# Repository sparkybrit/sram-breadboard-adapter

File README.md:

# sram-breadboard-adapter

An 8 MB SRAM board for a breadboard: eight Lyontek LY62W10248ML (1M × 8, TSOP-II-44) in two banks of
four, on a 4-layer board with +5V and GND planes. J0 carries the address and control lines, J1 the data.
Built for [Sparky1](https://github.com/sparkybrit/sparky1), a 68030 breadboard computer.

## Things the KiCad files do not tell you

**The byte lanes are numbered for a little-endian CPU.** In each bank, chip 0 is on D7–D0 and chip 3 on
D31–D24:

| Chip enable | J0 pin | Data lines |
|---|---|---|
| `/CEA0`, `/CEB0` | 24, 28 | D7–D0 |
| `/CEA1`, `/CEB1` | 25, 29 | D15–D8 |
| `/CEA2`, `/CEB2` | 26, 30 | D23–D16 |
| `/CEA3`, `/CEB3` | 27, 31 | D31–D24 |

The 68030 is big-endian: its byte 0 is on D31–D24. So on Sparky1 the chip selects are crossed over on the
breadboard: the select for the CPU's lane 0 goes to `/CEx3`, lane 1 to `/CEx2`, and so on. The data pins are
wired straight, D0 to D0.

**The fitted board has extra bypass capacitors that are not in the layout.** 100 nF 0402 parts were soldered
by hand straight across the supply pins of each RAM chip (2026-10-02; Sparky1's notes record one across
pins 11/12 and one across 33/34 on all eight). The layout's own capacitors sit off the end of each package,
too far from the pins: with them alone the board gave an occasional single-bit read error, and with the
extra ones it ran 127 hours clean. A new revision should place two capacitors per chip under the pins; see
"Improve decoupling capacitor placement" in Sparky1's `CLAUDE.md`.

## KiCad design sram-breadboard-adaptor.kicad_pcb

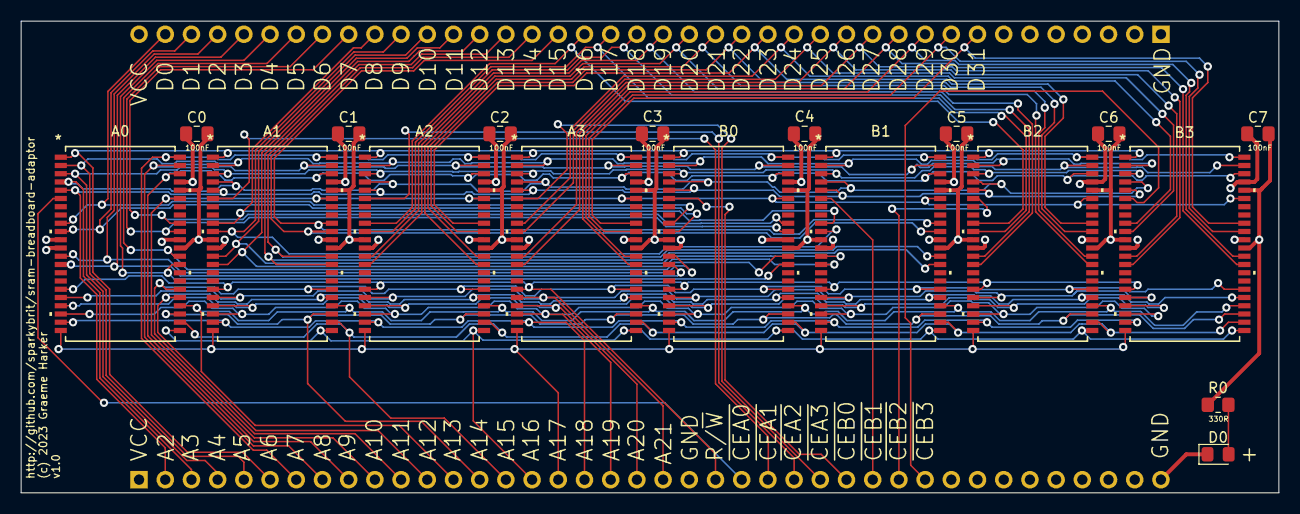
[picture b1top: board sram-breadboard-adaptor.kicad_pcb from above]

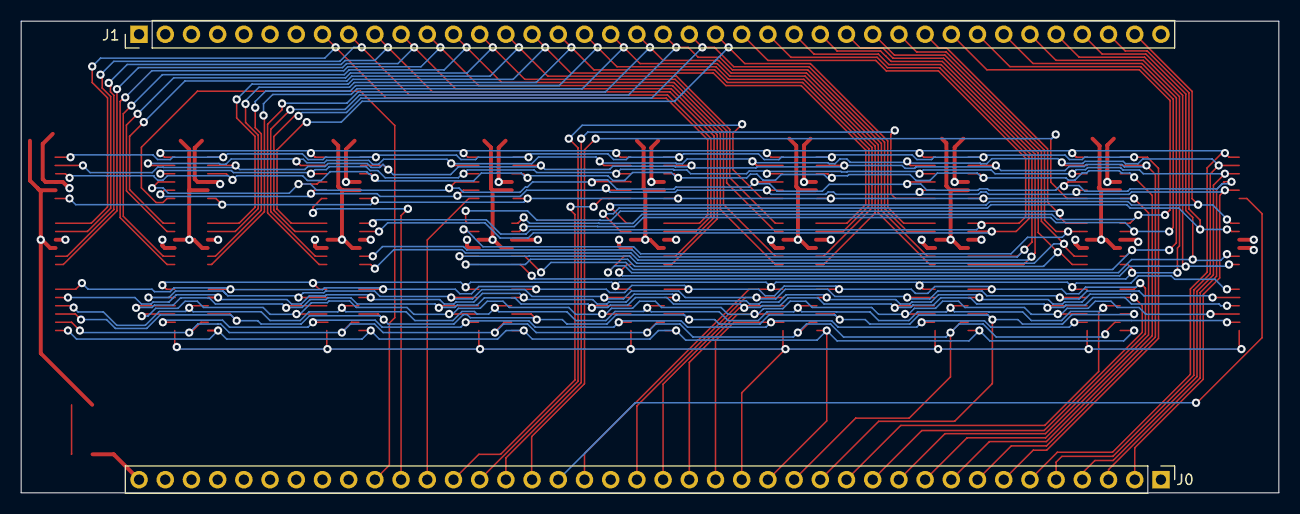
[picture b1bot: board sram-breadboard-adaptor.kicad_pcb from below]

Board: 4 copper layers, 121.9 x 45.7 mm, 20 parts (2 on the bottom side), 64 nets.

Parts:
A0, A1, A2, A3: LY62W10248ML-55LLI; TSOP-II-44_400MIL_LTK
B0, B1, B2, B3: LY62W10248ML-55LLI; TSOP-II-44_400MIL_LTK
C0, C2, C3, C4, C5, C6, C7: 100nF; C_0805_2012Metric_Pad1.18x1.45mm_HandSolder
C1: 110nF; C_0805_2012Metric_Pad1.18x1.45mm_HandSolder
D0: LED; LED_0805_2012Metric_Pad1.15x1.40mm_HandSolder
J0, J1: Conn_01x40; PinHeader_1x40_P2.54mm_Vertical
R0: 330R; R_0805_2012Metric_Pad1.20x1.40mm_HandSolder

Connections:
+5V: A0.11 (VCC), A0.33 (VCC), A0.40 (CE2), A1.11 (VCC), A1.33 (VCC), A1.40 (CE2), A2.11 (VCC), A2.33 (VCC), A2.40 (CE2), A3.11 (VCC), A3.33 (VCC), A3.40 (CE2), B0.11 (VCC), B0.33 (VCC), B0.40 (CE2), B1.11 (VCC), B1.33 (VCC), B1.40 (CE2), B2.11 (VCC), B2.33 (VCC), B2.40 (CE2), B3.11 (VCC), B3.33 (VCC), B3.40 (CE2), C0.1, C1.1, C2.1, C3.1, C4.1, C5.1, C6.1, C7.1, J0.1, J1.40, R0.1
/A2: A0.5 (A0), A1.5 (A0), A2.5 (A0), A3.5 (A0), B0.5 (A0), B1.5 (A0), B2.5 (A0), B3.5 (A0), J0.2
/A3: A0.4 (A1), A1.4 (A1), A2.4 (A1), A3.4 (A1), B0.4 (A1), B1.4 (A1), B2.4 (A1), B3.4 (A1), J0.3
/A4: A0.3 (A2), A1.3 (A2), A2.3 (A2), A3.3 (A2), B0.3 (A2), B1.3 (A2), B2.3 (A2), B3.3 (A2), J0.4
/A5: A0.2 (A3), A1.2 (A3), A2.2 (A3), A3.2 (A3), B0.2 (A3), B1.2 (A3), B2.2 (A3), B3.2 (A3), J0.5
/A6: A0.1 (A4), A1.1 (A4), A2.1 (A4), A3.1 (A4), B0.1 (A4), B1.1 (A4), B2.1 (A4), B3.1 (A4), J0.6
/A7: A0.44 (A5), A1.44 (A5), A2.44 (A5), A3.44 (A5), B0.44 (A5), B1.44 (A5), B2.44 (A5), B3.44 (A5), J0.7
/A8: A0.43 (A6), A1.43 (A6), A2.43 (A6), A3.43 (A6), B0.43 (A6), B1.43 (A6), B2.43 (A6), B3.43 (A6), J0.8
/A9: A0.42 (A7), A1.42 (A7), A2.42 (A7), A3.42 (A7), B0.42 (A7), B1.42 (A7), B2.42 (A7), B3.42 (A7), J0.9
/A10: A0.39 (A8), A1.39 (A8), A2.39 (A8), A3.39 (A8), B0.39 (A8), B1.39 (A8), B2.39 (A8), B3.39 (A8), J0.10
/A11: A0.28 (A9), A1.28 (A9), A2.28 (A9), A3.28 (A9), B0.28 (A9), B1.28 (A9), B2.28 (A9), B3.28 (A9), J0.11
/A12: A0.27 (A10), A1.27 (A10), A2.27 (A10), A3.27 (A10), B0.27 (A10), B1.27 (A10), B2.27 (A10), B3.27 (A10), J0.12
/A13: A0.26 (A11), A1.26 (A11), A2.26 (A11), A3.26 (A11), B0.26 (A11), B1.26 (A11), B2.26 (A11), B3.26 (A11), J0.13
/A14: A0.25 (A12), A1.25 (A12), A2.25 (A12), A3.25 (A12), B0.25 (A12), B1.25 (A12), B2.25 (A12), B3.25 (A12), J0.14
/A15: A0.24 (A13), A1.24 (A13), A2.24 (A13), A3.24 (A13), B0.24 (A13), B1.24 (A13), B2.24 (A13), B3.24 (A13), J0.15
/A16: A0.23 (A14), A1.23 (A14), A2.23 (A14), A3.23 (A14), B0.23 (A14), B1.23 (A14), B2.23 (A14), B3.23 (A14), J0.16
/A17: A0.22 (A15), A1.22 (A15), A2.22 (A15), A3.22 (A15), B0.22 (A15), B1.22 (A15), B2.22 (A15), B3.22 (A15), J0.17
/A18: A0.21 (A16), A1.21 (A16), A2.21 (A16), A3.21 (A16), B0.21 (A16), B1.21 (A16), B2.21 (A16), B3.21 (A16), J0.18
/A19: A0.20 (A17), A1.20 (A17), A2.20 (A17), A3.20 (A17), B0.20 (A17), B1.20 (A17), B2.20 (A17), B3.20 (A17), J0.19
/A20: A0.19 (A18), A1.19 (A18), A2.19 (A18), A3.19 (A18), B0.19 (A18), B1.19 (A18), B2.19 (A18), B3.19 (A18), J0.20
/A21: A0.18 (A19), A1.18 (A19), A2.18 (A19), A3.18 (A19), B0.18 (A19), B1.18 (A19), B2.18 (A19), B3.18 (A19), J0.21
/D0: A0.9 (DQ0), B0.9 (DQ0), J1.39
/D1: A0.10 (DQ1), B0.10 (DQ1), J1.38
/D2: A0.13 (DQ2), B0.13 (DQ2), J1.37
/D3: A0.14 (DQ3), B0.14 (DQ3), J1.36
/D4: A0.31 (DQ4), B0.31 (DQ4), J1.35
/D5: A0.32 (DQ5), B0.32 (DQ5), J1.34
/D6: A0.35 (DQ6), B0.35 (DQ6), J1.33
/D7: A0.36 (DQ7), B0.36 (DQ7), J1.32
/D8: A1.9 (DQ0), B1.9 (DQ0), J1.31
/D9: A1.10 (DQ1), B1.10 (DQ1), J1.30
/D10: A1.13 (DQ2), B1.13 (DQ2), J1.29
/D11: A1.14 (DQ3), B1.14 (DQ3), J1.28
/D12: A1.31 (DQ4), B1.31 (DQ4), J1.27
/D13: A1.32 (DQ5), B1.32 (DQ5), J1.26
/D14: A1.35 (DQ6), B1.35 (DQ6), J1.25
/D15: A1.36 (DQ7), B1.36 (DQ7), J1.24
/D16: A2.9 (DQ0), B2.9 (DQ0), J1.23
/D17: A2.10 (DQ1), B2.10 (DQ1), J1.22
/D18: A2.13 (DQ2), B2.13 (DQ2), J1.21
/D19: A2.14 (DQ3), B2.14 (DQ3), J1.20
/D20: A2.31 (DQ4), B2.31 (DQ4), J1.19
/D21: A2.32 (DQ5), B2.32 (DQ5), J1.18
/D22: A2.35 (DQ6), B2.35 (DQ6), J1.17
/D23: A2.36 (DQ7), B2.36 (DQ7), J1.16
/D24: A3.9 (DQ0), B3.9 (DQ0), J1.15
/D25: A3.10 (DQ1), B3.10 (DQ1), J1.14
/D26: A3.13 (DQ2), B3.13 (DQ2), J1.13
/D27: A3.14 (DQ3), B3.14 (DQ3), J1.12
/D28: A3.31 (DQ4), B3.31 (DQ4), J1.11
/D29: A3.32 (DQ5), B3.32 (DQ5), J1.10
/D30: A3.35 (DQ6), B3.35 (DQ6), J1.9
/D31: A3.36 (DQ7), B3.36 (DQ7), J1.8
/R/W: A0.17 (WE#), A1.17 (WE#), A2.17 (WE#), A3.17 (WE#), B0.17 (WE#), B1.17 (WE#), B2.17 (WE#), B3.17 (WE#), J0.23
/~CEA0: A0.6 (CE#), J0.24
/~CEA1: A1.6 (CE#), J0.25
/~CEA2: A2.6 (CE#), J0.26
/~CEA3: A3.6 (CE#), J0.27
/~CEB0: B0.6 (CE#), J0.28
/~CEB1: B1.6 (CE#), J0.29
/~CEB2: B2.6 (CE#), J0.30
/~CEB3: B3.6 (CE#), J0.31
GND: A0.12 (VSS), A0.34 (VSS), A0.41 (OE#), A1.12 (VSS), A1.34 (VSS), A1.41 (OE#), A2.12 (VSS), A2.34 (VSS), A2.41 (OE#), A3.12 (VSS), A3.34 (VSS), A3.41 (OE#), B0.12 (VSS), B0.34 (VSS), B0.41 (OE#), B1.12 (VSS), B1.34 (VSS), B1.41 (OE#), B2.12 (VSS), B2.34 (VSS), B2.41 (OE#), B3.12 (VSS), B3.34 (VSS), B3.41 (OE#), C0.2, C1.2, C2.2, C3.2, C4.2, C5.2, C6.2, C7.2, D0.1 (K), J0.22, J0.40, J1.1
unnamed: D0.2 (A), R0.2

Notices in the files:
sram-breadboard-adaptor.kicad_pcb:
(c) 2023 Graeme Harker
